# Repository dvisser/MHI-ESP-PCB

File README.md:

# MHI-ESP-PCB
ESP8266 based WiFi module for MHI split-system air conditioners that communicates directly with the air conditioner via the indoor unit PCB "CNS" (spi data) and "CNE" (display board data) connectors.

The "CNE" connection (between IR receiver board and the indoor unit control board) is to add features that are not accessible over the SPI connection on the "CNS" header (such as 3D Auto, some vane controls, etc).

This module is designed to run firmware developed jointly with TZB (thezerobeast) which is available here https://github.com/TheZeroBeast/ACWiFi

This PCB was designed and developed using KiCAD :-)

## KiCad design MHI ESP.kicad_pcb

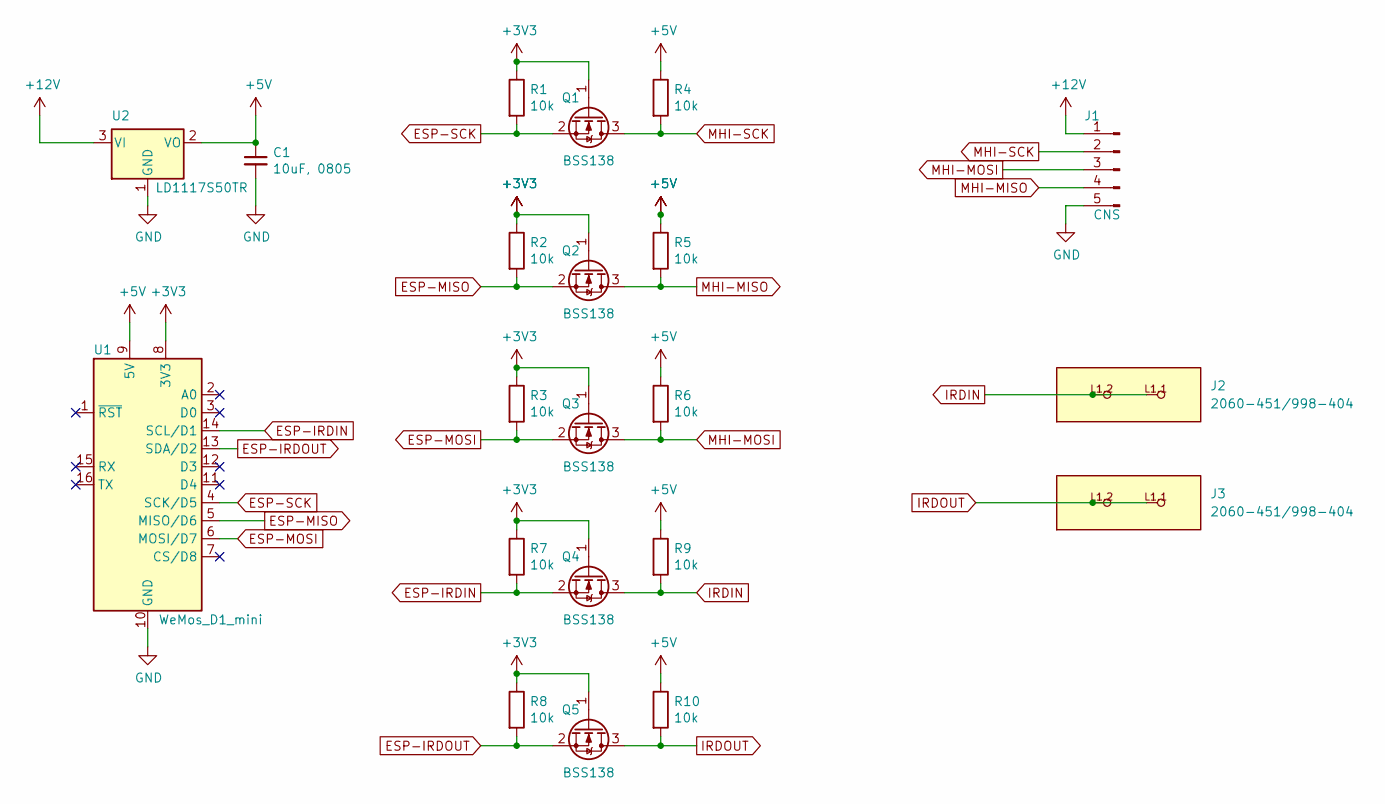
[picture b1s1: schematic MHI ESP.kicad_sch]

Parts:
C1: 10uF, 0805; C_0805_2012Metric
J1: CNS; JST_XH_B5B-XH-A_1x05_P2.50mm_Vertical
J2, J3: 2060-451/998-404; P-2060-451/998-404
Q1, Q2, Q3, Q4, Q5: BSS138; SOT-23
R1, R2, R3, R4, R5, R6, R7, R8, R9, R10: 10k; R_0805_2012Metric
U1: WeMos_D1_mini; WEMOS_D1_mini_light
U2: LD1117S50TR; SOT-223-3_TabPin2

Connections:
+3V3: Q1.1 (G), Q2.1 (G), Q3.1 (G), Q4.1 (G), Q5.1 (G), R1.1, R2.1, R3.1, R7.1, R8.1, U1.8 (3V3)
+5V: C1.1, R4.1, R5.1, R6.1, R9.1, R10.1, U1.9 (5V), U2.2 (VO)
+12V: J1.1, U2.3 (VI)
ESP-IRDIN: Q4.2 (S), R7.2, U1.14 (SCL/D1)
ESP-IRDOUT: Q5.2 (S), R8.2, U1.13 (SDA/D2)
ESP-MISO: Q2.2 (S), R2.2, U1.5 (MISO/D6)
ESP-MOSI: Q3.2 (S), R3.2, U1.6 (MOSI/D7)
ESP-SCK: Q1.2 (S), R1.2, U1.4 (SCK/D5)
GND: C1.2, J1.5, U1.10 (GND), U2.1 (GND)
IRDIN: J2.L1.1, J2.L1.2, Q4.3 (D), R9.2
IRDOUT: J3.L1.1, J3.L1.2, Q5.3 (D), R10.2
MHI-MISO: J1.4, Q2.3 (D), R5.2
MHI-MOSI: J1.3, Q3.3 (D), R6.2
MHI-SCK: J1.2, Q1.3 (D), R4.2

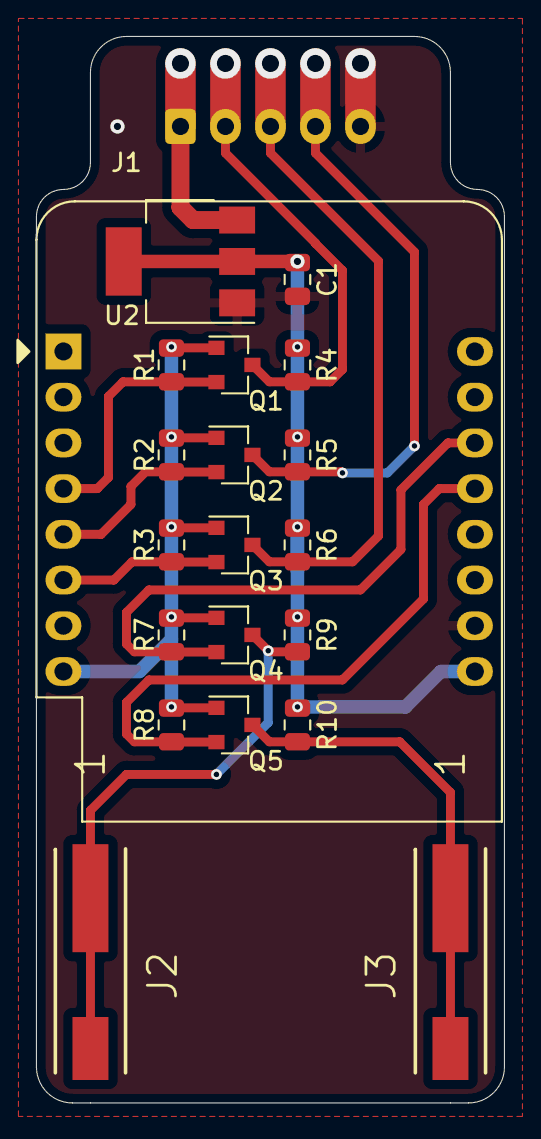
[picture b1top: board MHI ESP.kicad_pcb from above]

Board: 2 copper layers, 26.0 x 59.2 mm, 21 parts (1 on the bottom side), 14 nets.

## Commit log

2021-09-08 Remove TXB0104 IC, DS18B20 IC and change 5V IC
2021-09-08 Re-annotate schematic and update components on PCB, ready for new track layout
2021-09-08 Update connector footprint to 05JQ-BT to accomodate non-cabled installs
2021-09-08 Ready to route PCB v2.0
2021-09-08 PCB v2.0 - routing completed
2021-09-10 Minor silkscreen updates and Gerber / Drill File Generation
2021-09-10 Create LICENSE
2021-09-10 Update issue templates
2021-09-12 Start of IR data capturing idea...
2021-09-13 Reconfigured J2 and J3 to suit cable out to CNE.
2021-09-14 Added IR data injection circuit and headers
2021-09-14 corrected J2 and J3 designator visibility
2021-09-14 Added PDF schematic
2021-10-05 Add images for readme.md
2022-01-15 Update README.md
    add missing info regarding what CNE connection is used for and why
2023-01-06 Updated to v4.0
    Added WAGO terminals for IR signal in and out.
